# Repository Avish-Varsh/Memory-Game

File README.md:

# Simon-style Retro Memory Game 

# Project Status

✅ **Full release** 

## Current version

**Version: v1.1.0**

_Latest update: High-score storage_

Current features:
- 100 levels 
- High-score storage
- Fully playable game loop
- Random sequence generation
- Player input validation
- Progressive difficulty
- Win/Loss sequences 
- Unique audio feedback on player input
- Startup melody 
- Custom multi level with visible circuit design PCB
- Battery powered usability 

## Overview

This project is a Simon-style memory game built using an Arduino Uno. The player must memorize and repeat an increasingly long sequence of colored LEDs using the corresponding push buttons.

The project focuses on embedded systems programming, finite state machines, input validation, timing control and modular code design. It is being developed incrementally, with each version introducing new gameplay mechanics and hardware features. Development is being tracked using Git for versioning to document project progression.

📹 **[Gameplay Demo (Breadboard)](evidence/demo_v1.mp4)**

## Important Note
To make sure this project is accessible to as many people as possible. I have used an visible circuit design without a proper enclosure and rather used the PCB itself as an enclosure to preserve the retro feel of the product and ensure anyone with any kind of components can create and use it. As the a case would require strict measurements and only certain parts to be used. I don't intend to turn this into a consumer grade product, if anyone feels like they would like to please fell free as long as you credit me in the design.  

## Gameplay Overview:
At startup, a random sequence of LEDs is displayed. The player must replicate the sequence using the corresponding colored buttons. Each successful round increases the difficulty by extending the sequence length and increasing the playback speed. If the player enters an incorrect sequence at any point, the game ends and they must restart the game.

## Bill of Materials (BOM)

| Qty | Component | Value / Part | Description |
|---:|------------|--------------|-------------|
| 1 | Arduino Nano | Arduino Nano v3.x | Main microcontroller |
| 1 | 9 V Battery | — | Power source |
| 1 | Piezo Buzzer | — | Polarized buzzer for audio feedback |
| 1 | Red LED | — | Visual feedback |
| 1 | Green LED | — | Visual feedback |
| 1 | Blue LED | — | Visual feedback |
| 3 | Resistors | 220 Ω | Current-limiting resistors for LEDs |
| 1 | 10 kΩ Potentiometer | B10K | Linear potentiometer |
| 1 | Red Push Button | SW_Push | User input |
| 1 | Green Push Button | SW_Push | User input |
| 1 | Blue Push Button | SW_Push | User input |
| 1 | Power Switch | SPST | Main power switch |
| 1 | 1×8 Pin Header | Male | Board-to-board connector |
| 1 | 1×8 Socket Header | Female | Board-to-board connector |
| 1 | 1×1 Pin Header | Male | Single-pin connector |
| 1 | 1×1 Socket Header | Female | Single-pin connector |

# Progress Roadmap:

## Section 1: Planning

* [x] Define project concept
* [x] Select components
* [x] Create GitHub repository
* [x] Create initial project structure
* [x] Draft wiring schematic

## Section 2: Core Hardware

* [x] Connect LEDs and verify operation
* [x] Connect buttons and verify input
* [x] Connect buzzer and verify sound output
* [x] Build and test complete circuit

## Section 3: Core Game Logic

* [x] Generate random sequences
* [x] Display sequence to player
* [x] Read player input
* [x] Validate player input
* [x] Implement win/lose conditions
* [x] Add score tracking
* [x] Add correct game progression

## Section 4: Difficulty System

* [x] Increase sequence length each level
* [x] Add potentiometer to control LED blink speed
* [x] Balance game difficulty

## Section 5: Audio Feedback

* [x] Add unique tones for each button
* [x] Add correct input feedback
* [x] Add loss melody
* [x] Add startup melody
* [x] Add win melody

## Section 6: Enclosure Design 

* [x] Create initial enclosure concept
* [x] Design button layout
* [x] Design LED placement
* [x] Create custom PCB
* [x] Create enclosure v1
* [x] Refine enclosure based on testing
* [x] Finalize enclosure design

## Section 7: Testing & Optimization

* [x] Test all game functions
* [x] Fix identified bugs
* [x] Improve code organization
* [x] Perform final hardware verification

## Section 8: Documentation

* [x] Create final schematic
* [x] Add circuit images
* [x] Add project photos
* [x] Document challenges faced
* [x] Document lessons learned
* [x] Complete README

## Challenges Faced

- Designing a reliable input validation system while preventing accidental multiple button presses.
- Debugging state transition issues that caused the game logic to become inconsistent.
- Resolving timing conflicts between LED animations and player input.
- Preventing invalid variable values caused by unintended state changes.
- Structuring the code into reusable functions to improve maintainability.
- Finding accurate part footprints.
- Aligning parts to create multi level PCB
- Making sure High-score was only set to 0 on first boot. 

> Additional challenges will be documented as development continues.

## Skills Learned

- Finite State Machine (FSM) design
- Edge detection for button input
- Software debouncing techniques
- Modular programming using custom functions
- Enum-based state management
- Switch-case driven program flow
- Random sequence generation
- Timing management using millis()
- Debugging embedded software
- Hardware/software integration
- Multi level PCB design 
- Using EEPROM for storage of important variables.  

> Additional skills will be documented as development continues.

## Section 9: Future Improvements
* [x] Add  EEPROM to save important user data such as high scores
* [ ] Add LCD for live feedback
* [ ] Create custom win/loss screens for the LCD
* [ ] Add an LED matrix to increase difficulty as sequences can come from a bigger space and in a harder to remember pattern
* [ ] Add a charging feature to improve portability
* [ ] Multiple gameplay modes
* [ ] Use ESP32 instead of Arduino to link the game to an online leaderboard

## Images

### Hardware Prototype v1

### Hardware Prototype v2

## Version History

### v1.1.0
- Maximum 100 levels
- High-score storage 

### v1.0.0
- Multi level PCB
- Visible circuit design

### v0.6.0
- Custom PCB 
- Battery power 

### v0.5.0
- Added unique audio feedback for each button
- Added startup melody
- Added win melody
- Added loss melody
- Integrated audio feedback into gameplay

### v0.4.0
- Playable beta release
- Added input validation
- Added win/lose sequences
- Improved game progression

### v0.3.0
- Added score tracking
- Added progressive difficulty using random sequences that increase in length after each successful round 
- Added a potentiometer to control LED speed

### v0.2.0
- Initial hardware prototype and schematic

### v0.1.0
- Initial planning

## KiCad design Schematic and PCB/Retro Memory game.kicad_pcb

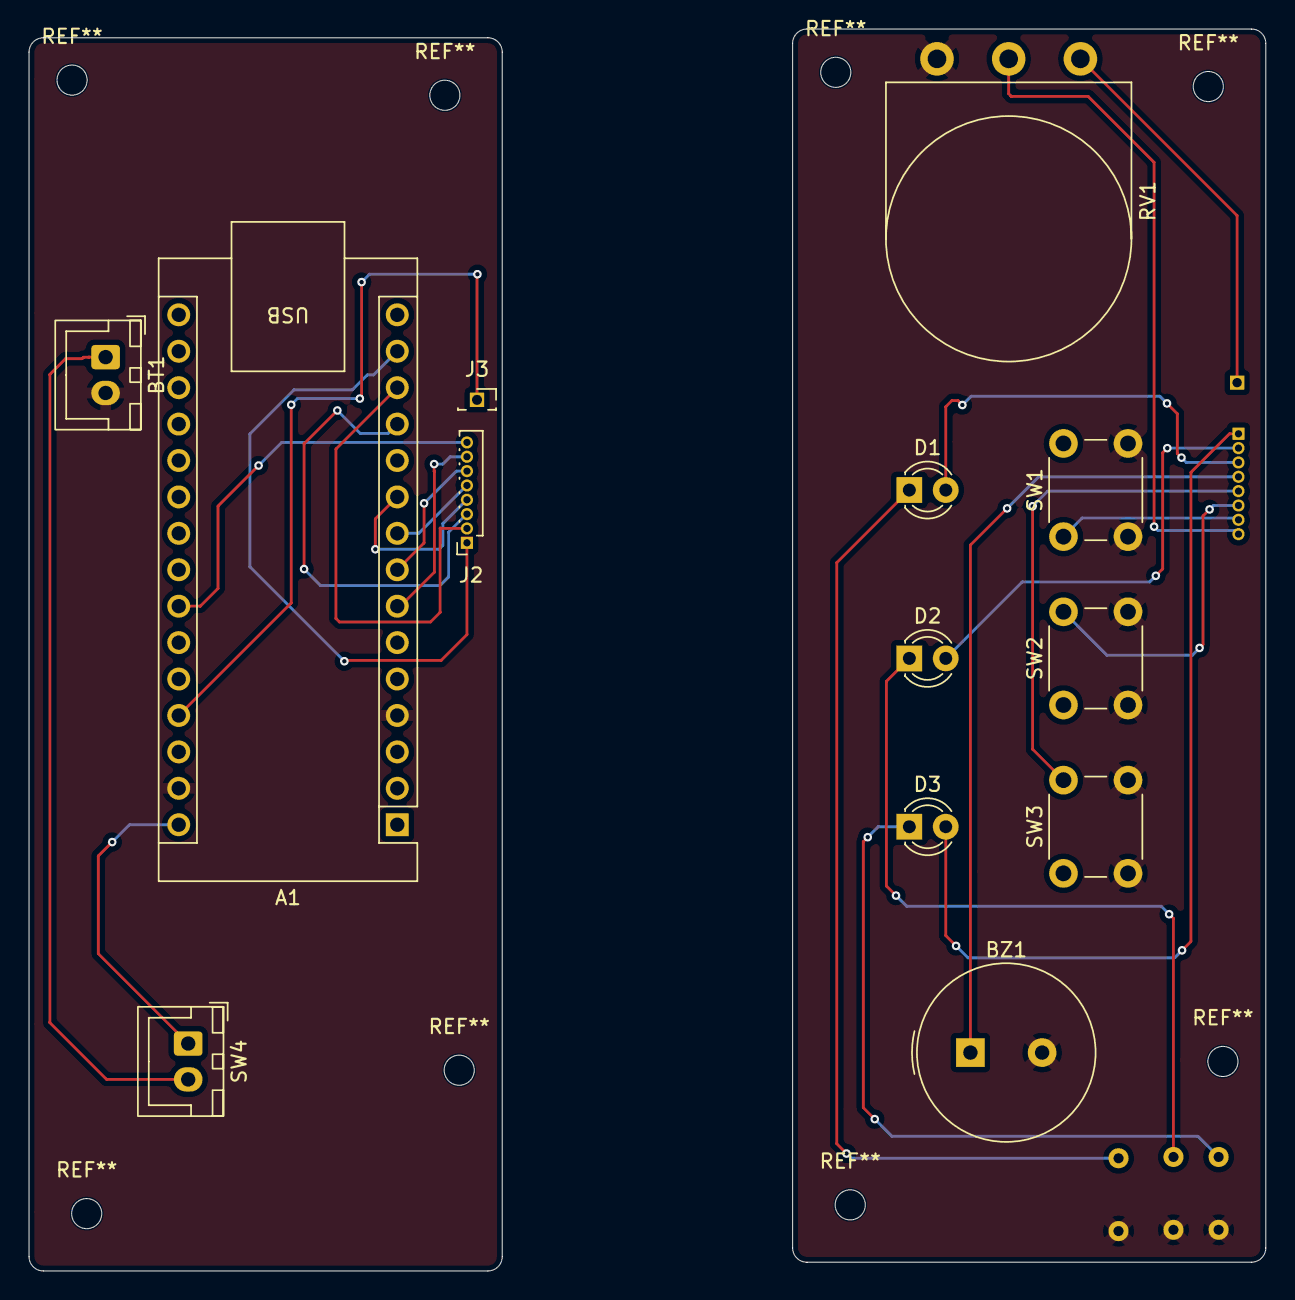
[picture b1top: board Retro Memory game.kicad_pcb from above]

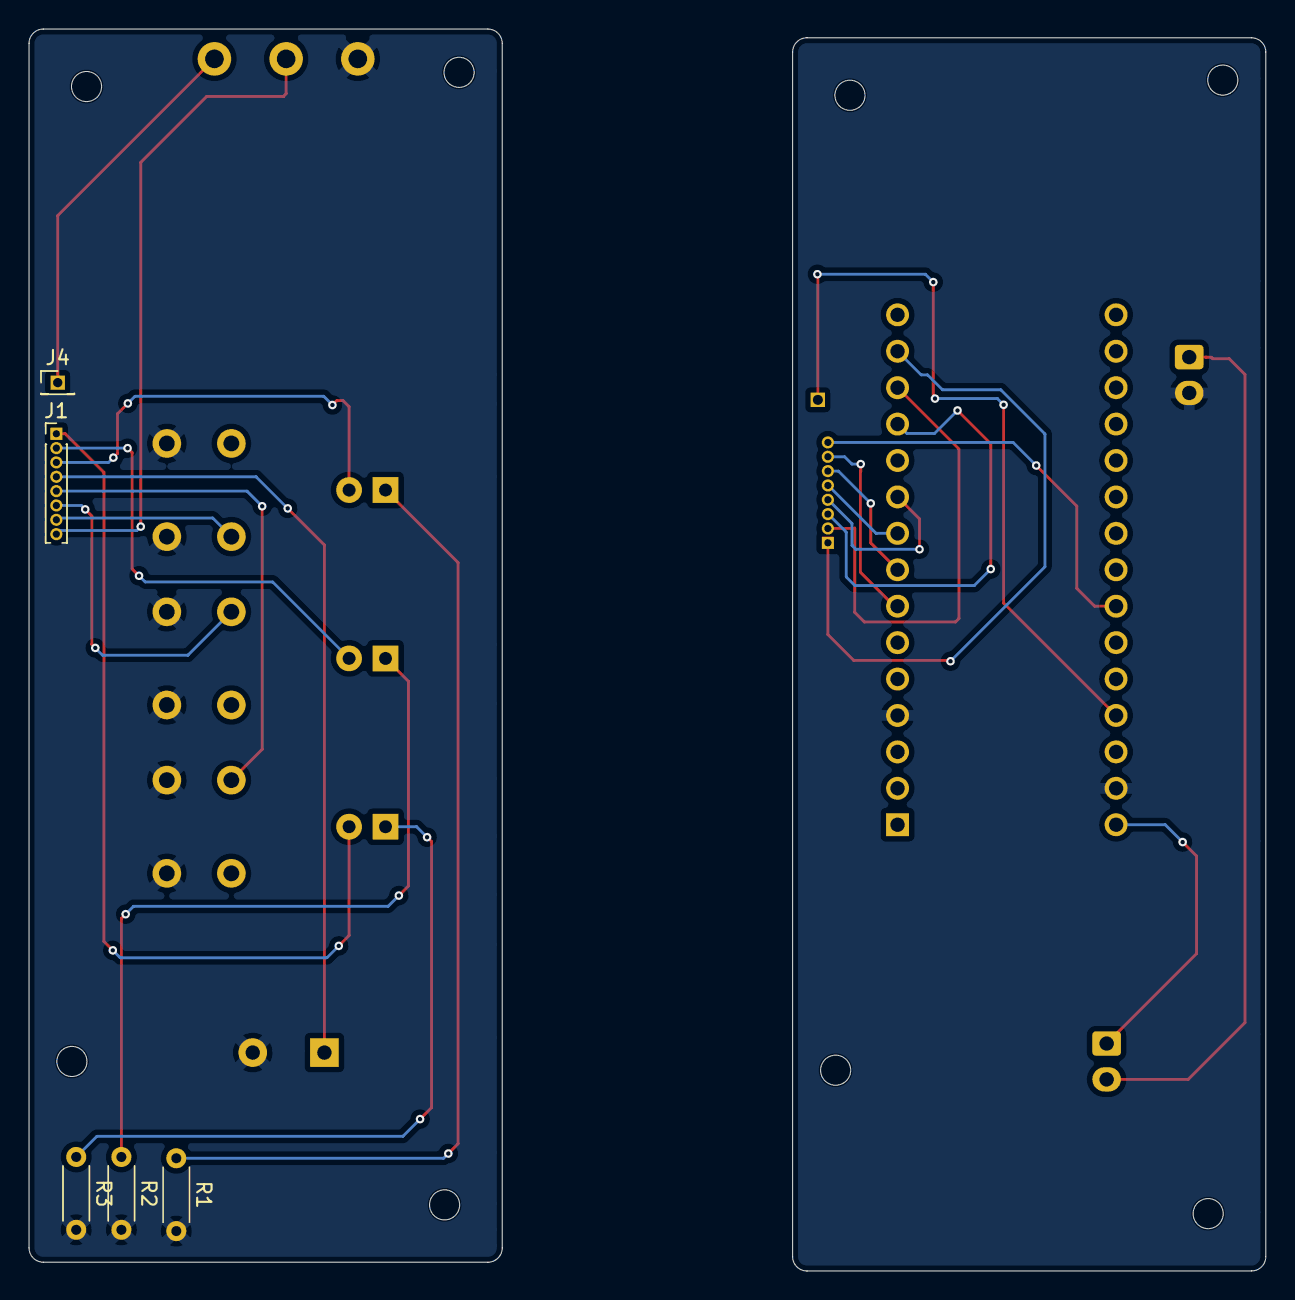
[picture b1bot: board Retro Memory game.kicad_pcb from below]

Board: 2 copper layers, 86.2 x 86.6 mm, 18 parts (5 on the bottom side), 24 nets.

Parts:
A1: Arduino_Nano_v3.x; Arduino_Nano
BT1: Battery_Cell; JST_XH_B2B-XH-A_1x02_P2.50mm_Vertical
BZ1: Buzzer; Buzzer_TDK_PS1240P02BT_D12.2mm_H6.5mm
D1, D2, D3: LED; LED_D3.0mm
J1: Conn_01x08_Pin; PinHeader_1x08_P1.00mm_Vertical
J2: Conn_01x08_Socket; PinSocket_1x08_P1.00mm_Vertical
J3: Conn_01x01_Socket; PinSocket_1x01_P1.27mm_Vertical
J4: Conn_01x01_Pin; PinHeader_1x01_P1.27mm_Vertical
R1, R2, R3: 220 ohms; R_Axial_DIN0204_L3.6mm_D1.6mm_P5.08mm_Horizontal
RV1: B 10k; Potentiometer_Omeg_PC16BU_Vertical
SW1, SW2, SW3: SW_Push; SW_PUSH_6mm
SW4: SW_SPST; JST_XH_B2B-XH-A_1x02_P2.50mm_Vertical

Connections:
+5V: A1.27 (+5V), J3.1 (Pin_1_1)
/5v: J4.1 (Pin_1_1), RV1.3
/7: A1.7 (D4), J2.7
/8: A1.8 (D5), J2.6
/9: A1.9 (D6), J2.5
/10: A1.10 (D7), J2.4
/12: A1.12 (D9), J2.3
/13: A1.13 (D10), J2.2
/14: A1.14 (D11), J2.1
/24: A1.24 (A5), J2.8
/A5: J1.8, RV1.2
/D4: J1.7, SW1.1
/D5: J1.6, SW2.1
/D6: J1.5, SW3.1
/D7: BZ1.1 (+), J1.4
/D9: D1.2 (A), J1.3
/D10: D2.2 (A), J1.2
/D11: D3.2 (A), J1.1
GND: A1.4 (GND), A1.29 (GND), BT1.2 (-), BZ1.2 (-), R1.2, R2.2, R3.2, RV1.1, SW1.2, SW2.2, SW3.2
unnamed: A1.30 (VIN), SW4.1 (A)
unnamed: BT1.1 (+), SW4.2 (B)
unnamed: D1.1 (K), R1.1
unnamed: D2.1 (K), R2.1
unnamed: D3.1 (K), R3.1

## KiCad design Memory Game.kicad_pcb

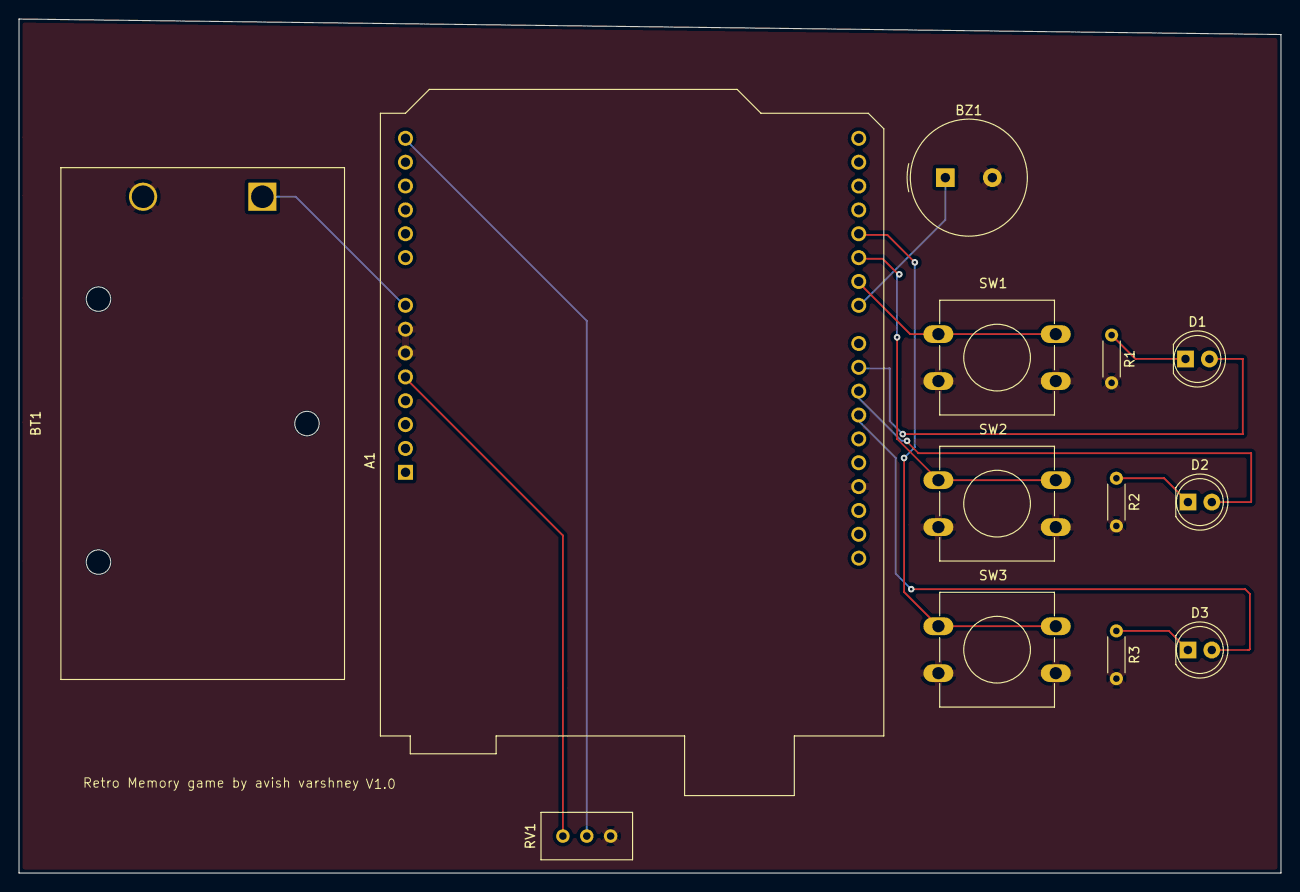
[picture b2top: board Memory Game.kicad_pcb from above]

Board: 4 copper layers, 134.4 x 90.9 mm, 13 parts (0 on the bottom side), 14 nets.

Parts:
A1: Arduino_UNO_R3
BT1: Battery 9v; BatteryHolder_Eagle_12BH611-GR
BZ1: Buzzer; Buzzer_TDK_PS1240P02BT_D12.2mm_H6.5mm
D1, D2, D3: LED; LED_D5.0mm
R1, R2, R3: 220 Ω; R_Axial_DIN0204_L3.6mm_D1.6mm_P5.08mm_Horizontal
RV1: R_Potentiometer B10K; Potentiometer_Bourns_3386C_Horizontal
SW1, SW2, SW3: SW_Push; SW_PUSH-12mm

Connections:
+5V: A1.5 (+5V), RV1.1
/Btn 1: A1.19 (D4), SW3.1
/Btn 2: A1.20 (D5), SW2.1
/Btn 3: A1.21 (D6), SW1.1
/LED 1: A1.24 (D9), D1.2 (A)
/LED 2: A1.25 (D10), D2.2 (A)
/LED 3: A1.26 (D11), D3.2 (A)
/buzz: A1.22 (D7), BZ1.1 (+)
GND: A1.6 (GND), A1.7 (GND), A1.29 (GND), BT1.2 (-), BZ1.2 (-), R1.2, R2.2, R3.2, RV1.3, SW1.2, SW2.2, SW3.2
unnamed: A1.14 (SCL/A5), RV1.2
unnamed: A1.8 (VIN), BT1.1 (+)
unnamed: D1.1 (K), R1.1
unnamed: D2.1 (K), R2.1
unnamed: D3.1 (K), R3.1

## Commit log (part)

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2026-06-24 Initialize README with project details and roadmap
    Added detailed project information, including goals, components, planned features, and a roadmap for development.
2026-06-24 Add schematic and Hardware v1 picture Complete v0.2.0
2026-06-25 Add led sequence and potentiometer v0.3.0
2026-06-29 v0.4.0 beta release
2026-06-29 README and lose sequence changes
2026-06-30 v0.5.0 beta release with Audio Feedback
